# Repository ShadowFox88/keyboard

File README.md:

# Keyboard

This is a repo with the files used to make my own mechanical keyboard.

Why? It seemed like a fun project to do.

A journal of the time spent is available at report/report.pdf.

I used KiCad, and Fusion360 for this, and had to learn both of them.
All images are in the report.

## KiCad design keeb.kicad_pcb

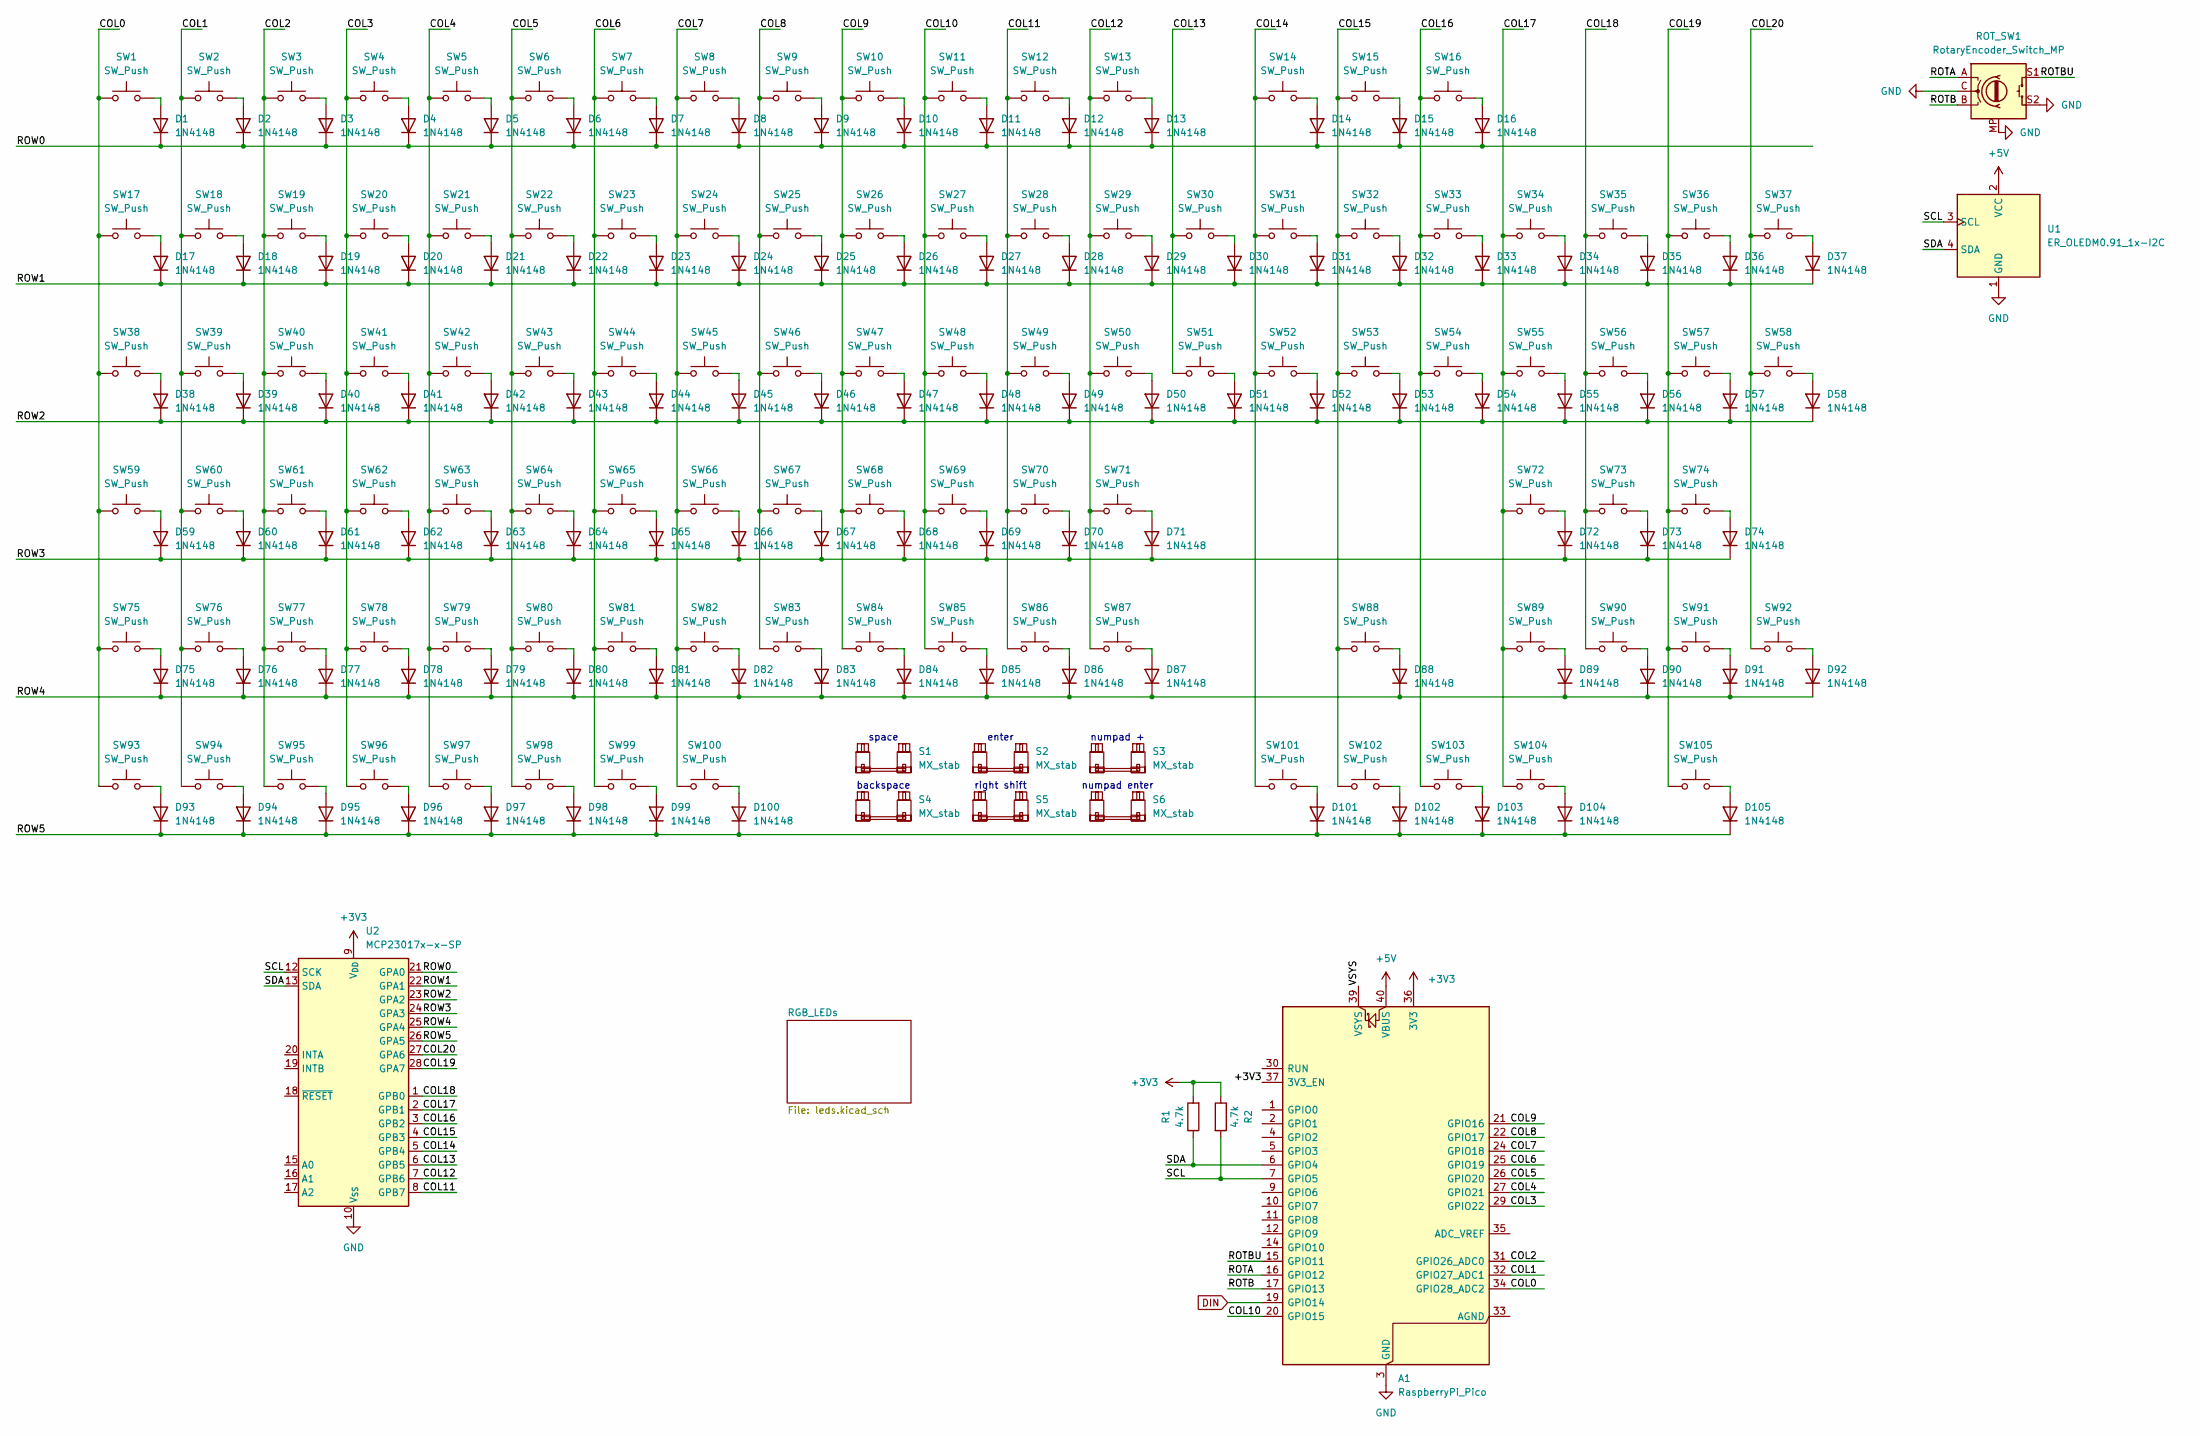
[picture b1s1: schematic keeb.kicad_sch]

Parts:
A1: RaspberryPi_Pico; RaspberryPi_Pico_Common_THT
D1, D2, D3, D4, D5, D6, D7, D8, D9, D10, D11, D12, D13, D14, D15, D16, D17, D18, D19, D20, D21, D22, D23, D24, D25, D26, D27, D28, D29, D30, D31, D32, D33, D34, D35, D36, D37, D38, D39, D40, D41, D42, D43, D44, D45, D46, D47, D48, D49, D50, D51, D52, D53, D54, D55, D56, D57, D58, D59, D60, D61, D62, D63, D64, D65, D66, D67, D68, D69, D70, D71, D72, D73, D74, D75, D76, D77, D78, D79, D80, D81, D82, D83, D84, D85, D86, D87, D88, D89, D90, D91, D92, D93, D94, D95, D96, D97, D98, D99, D100, D101, D102, D103, D104, D105: 1N4148; D_SOD-123F
R1, R2: 4.7k; R_Axial_DIN0207_L6.3mm_D2.5mm_P7.62mm_Horizontal
ROT_SW1: RotaryEncoder_Switch_MP; RotaryEncoder_Alps_EC12E-Switch_Vertical_H20mm
S1: MX_stab; STAB_MX_6.25u
S2: MX_stab; STAB_MX_ISO
S3, S4, S6: MX_stab; STAB_MX_2u
S5: MX_stab; STAB_MX_2.75u
SW1, SW2, SW3, SW4, SW5, SW6, SW7, SW8, SW9, SW10, SW11, SW12, SW13, SW14, SW15, SW16, SW17, SW18, SW19, SW20, SW21, SW22, SW23, SW24, SW25, SW26, SW27, SW28, SW29, SW30, SW31, SW32, SW33, SW34, SW35, SW36, SW37, SW38, SW39, SW40, SW41, SW42, SW43, SW44, SW45, SW46, SW47, SW48, SW49, SW50, SW51, SW52, SW53, SW54, SW55, SW56, SW57, SW58, SW59, SW60, SW61, SW62, SW63, SW64, SW65, SW66, SW67, SW68, SW69, SW70, SW71, SW72, SW73, SW74, SW75, SW76, SW77, SW78, SW79, SW80, SW81, SW82, SW83, SW84, SW85, SW86, SW87, SW88, SW89, SW90, SW91, SW92, SW93, SW94, SW95, SW96, SW97, SW98, SW99, SW100, SW101, SW102, SW103, SW104, SW105: SW_Push; SW_MX_HS_CPG151101S11_1u
U1: ER_OLEDM0.91_1x-I2C
U2: MCP23017x-x-SP; DIP-28_W7.62mm

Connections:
+3V3: A1.36 (3V3), A1.37 (3V3_EN), R1.2, R2.1, U2.9 (V_{DD})
+5V: A1.40 (VBUS), U1.2 (VCC); also elsewhere on the board
/COL0: A1.34 (GPIO28_ADC2), SW1.1, SW17.1, SW38.1, SW59.1, SW75.1, SW93.1
/COL1: A1.32 (GPIO27_ADC1), SW2.1, SW18.1, SW39.1, SW60.1, SW76.1, SW94.1
/COL2: A1.31 (GPIO26_ADC0), SW3.1, SW19.1, SW40.1, SW61.1, SW77.1, SW95.1
/COL3: A1.29 (GPIO22), SW4.1, SW20.1, SW41.1, SW62.1, SW78.1, SW96.1
/COL4: A1.27 (GPIO21), SW5.1, SW21.1, SW42.1, SW63.1, SW79.1, SW97.1
/COL5: A1.26 (GPIO20), SW6.1, SW22.1, SW43.1, SW64.1, SW80.1, SW98.1
/COL6: A1.25 (GPIO19), SW7.1, SW23.1, SW44.1, SW65.1, SW81.1, SW99.1
/COL7: A1.24 (GPIO18), SW8.1, SW24.1, SW45.1, SW66.1, SW82.1, SW100.1
/COL8: A1.22 (GPIO17), SW9.1, SW25.1, SW46.1, SW67.1, SW83.1
/COL9: A1.21 (GPIO16), SW10.1, SW26.1, SW47.1, SW68.1, SW84.1
/COL10: A1.20 (GPIO15), SW11.1, SW27.1, SW48.1, SW69.1, SW85.1
/COL11: SW12.1, SW28.1, SW49.1, SW70.1, SW86.1, U2.8 (GPB7)
/COL12: SW13.1, SW29.1, SW50.1, SW71.1, SW87.1, U2.7 (GPB6)
/COL13: SW30.1, SW51.1, U2.6 (GPB5)
/COL14: SW14.1, SW31.1, SW52.1, SW101.1, U2.5 (GPB4)
/COL15: SW15.1, SW32.1, SW53.1, SW88.1, SW102.1, U2.4 (GPB3)
/COL16: SW16.1, SW33.1, SW54.1, SW103.1, U2.3 (GPB2)
/COL17: SW34.1, SW55.1, SW72.1, SW89.1, SW104.1, U2.2 (GPB1)
/COL18: SW35.1, SW56.1, SW73.1, SW90.1, U2.1 (GPB0)
/COL19: SW36.1, SW57.1, SW74.1, SW91.1, SW105.1, U2.28 (GPA7)
/COL20: SW37.1, SW58.1, SW92.1, U2.27 (GPA6)
/ROTA: A1.16 (GPIO12), ROT_SW1.A
/ROTB: A1.17 (GPIO13), ROT_SW1.B
/ROTBU: A1.15 (GPIO11), ROT_SW1.S1
/ROW0: D1.1 (K), D2.1 (K), D3.1 (K), D4.1 (K), D5.1 (K), D6.1 (K), D7.1 (K), D8.1 (K), D9.1 (K), D10.1 (K), D11.1 (K), D12.1 (K), D13.1 (K), D14.1 (K), D15.1 (K), D16.1 (K), U2.21 (GPA0)
/ROW1: D17.1 (K), D18.1 (K), D19.1 (K), D20.1 (K), D21.1 (K), D22.1 (K), D23.1 (K), D24.1 (K), D25.1 (K), D26.1 (K), D27.1 (K), D28.1 (K), D29.1 (K), D30.1 (K), D31.1 (K), D32.1 (K), D33.1 (K), D34.1 (K), D35.1 (K), D36.1 (K), D37.1 (K), U2.22 (GPA1)
/ROW2: D38.1 (K), D39.1 (K), D40.1 (K), D41.1 (K), D42.1 (K), D43.1 (K), D44.1 (K), D45.1 (K), D46.1 (K), D47.1 (K), D48.1 (K), D49.1 (K), D50.1 (K), D51.1 (K), D52.1 (K), D53.1 (K), D54.1 (K), D55.1 (K), D56.1 (K), D57.1 (K), D58.1 (K), U2.23 (GPA2)
/ROW3: D59.1 (K), D60.1 (K), D61.1 (K), D62.1 (K), D63.1 (K), D64.1 (K), D65.1 (K), D66.1 (K), D67.1 (K), D68.1 (K), D69.1 (K), D70.1 (K), D71.1 (K), D72.1 (K), D73.1 (K), D74.1 (K), U2.24 (GPA3)
/ROW4: D75.1 (K), D76.1 (K), D77.1 (K), D78.1 (K), D79.1 (K), D80.1 (K), D81.1 (K), D82.1 (K), D83.1 (K), D84.1 (K), D85.1 (K), D86.1 (K), D87.1 (K), D88.1 (K), D89.1 (K), D90.1 (K), D91.1 (K), D92.1 (K), U2.25 (GPA4)
/ROW5: D93.1 (K), D94.1 (K), D95.1 (K), D96.1 (K), D97.1 (K), D98.1 (K), D99.1 (K), D100.1 (K), D101.1 (K), D102.1 (K), D103.1 (K), D104.1 (K), D105.1 (K), U2.26 (GPA5)
/SCL: A1.7 (GPIO5), R2.2, U1.3 (SCL), U2.12 (SCK)
/SDA: A1.6 (GPIO4), R1.1, U1.4 (SDA), U2.13 (SDA)
/VSYS: A1.39 (VSYS)
DIN: A1.19 (GPIO14); also elsewhere on the board
GND: A1.3 (GND), A1.8 (GND), A1.13 (GND), A1.18 (GND), A1.23 (GND), A1.28 (GND), A1.38 (GND), ROT_SW1.C, ROT_SW1.MP, ROT_SW1.S2, U1.1 (GND), U2.10 (V_{SS}); also elsewhere on the board
unnamed: D1.2 (A), SW1.2
unnamed: D2.2 (A), SW2.2
unnamed: D3.2 (A), SW3.2
unnamed: D4.2 (A), SW4.2
unnamed: D5.2 (A), SW5.2
unnamed: D6.2 (A), SW6.2
unnamed: D7.2 (A), SW7.2
unnamed: D8.2 (A), SW8.2
unnamed: D9.2 (A), SW9.2
unnamed: D10.2 (A), SW10.2
unnamed: D11.2 (A), SW11.2
unnamed: D12.2 (A), SW12.2
unnamed: D13.2 (A), SW13.2
unnamed: D14.2 (A), SW14.2
unnamed: D15.2 (A), SW15.2
unnamed: D16.2 (A), SW16.2
unnamed: D17.2 (A), SW17.2
unnamed: D18.2 (A), SW18.2
unnamed: D19.2 (A), SW19.2
unnamed: D20.2 (A), SW20.2
unnamed: D21.2 (A), SW21.2
unnamed: D22.2 (A), SW22.2
unnamed: D23.2 (A), SW23.2
unnamed: D24.2 (A), SW24.2
unnamed: D25.2 (A), SW25.2
unnamed: D26.2 (A), SW26.2
unnamed: D27.2 (A), SW27.2
unnamed: D28.2 (A), SW28.2
unnamed: D29.2 (A), SW29.2
unnamed: D30.2 (A), SW30.2
unnamed: D31.2 (A), SW31.2
unnamed: D32.2 (A), SW32.2
unnamed: D33.2 (A), SW33.2
unnamed: D34.2 (A), SW34.2
unnamed: D35.2 (A), SW35.2
unnamed: D36.2 (A), SW36.2
unnamed: D37.2 (A), SW37.2
unnamed: D38.2 (A), SW38.2
unnamed: D39.2 (A), SW39.2
unnamed: D40.2 (A), SW40.2
unnamed: D41.2 (A), SW41.2
unnamed: D42.2 (A), SW42.2
unnamed: D43.2 (A), SW43.2
unnamed: D44.2 (A), SW44.2
unnamed: D45.2 (A), SW45.2
unnamed: D46.2 (A), SW46.2
unnamed: D47.2 (A), SW47.2
unnamed: D48.2 (A), SW48.2
unnamed: D49.2 (A), SW49.2
unnamed: D50.2 (A), SW50.2
unnamed: D51.2 (A), SW51.2
unnamed: D52.2 (A), SW52.2
unnamed: D53.2 (A), SW53.2
unnamed: D54.2 (A), SW54.2
unnamed: D55.2 (A), SW55.2
unnamed: D56.2 (A), SW56.2
unnamed: D57.2 (A), SW57.2
unnamed: D58.2 (A), SW58.2
unnamed: D59.2 (A), SW59.2
unnamed: D60.2 (A), SW60.2
unnamed: D61.2 (A), SW61.2
unnamed: D62.2 (A), SW62.2
unnamed: D63.2 (A), SW63.2
unnamed: D64.2 (A), SW64.2
unnamed: D65.2 (A), SW65.2
unnamed: D66.2 (A), SW66.2
unnamed: D67.2 (A), SW67.2
unnamed: D68.2 (A), SW68.2
unnamed: D69.2 (A), SW69.2
unnamed: D70.2 (A), SW70.2
unnamed: D71.2 (A), SW71.2
unnamed: D72.2 (A), SW72.2
unnamed: D73.2 (A), SW73.2
unnamed: D74.2 (A), SW74.2
unnamed: D75.2 (A), SW75.2
unnamed: D76.2 (A), SW76.2
unnamed: D77.2 (A), SW77.2
unnamed: D78.2 (A), SW78.2
unnamed: D79.2 (A), SW79.2
unnamed: D80.2 (A), SW80.2
unnamed: D81.2 (A), SW81.2
unnamed: D82.2 (A), SW82.2
unnamed: D83.2 (A), SW83.2
unnamed: D84.2 (A), SW84.2
unnamed: D85.2 (A), SW85.2
unnamed: D86.2 (A), SW86.2
unnamed: D87.2 (A), SW87.2
unnamed: D88.2 (A), SW88.2
unnamed: D89.2 (A), SW89.2
unnamed: D90.2 (A), SW90.2
unnamed: D91.2 (A), SW91.2
unnamed: D92.2 (A), SW92.2
unnamed: D93.2 (A), SW93.2
unnamed: D94.2 (A), SW94.2
unnamed: D95.2 (A), SW95.2
unnamed: D96.2 (A), SW96.2
unnamed: D97.2 (A), SW97.2
unnamed: D98.2 (A), SW98.2
unnamed: D99.2 (A), SW99.2
unnamed: D100.2 (A), SW100.2
unnamed: D101.2 (A), SW101.2
unnamed: D102.2 (A), SW102.2
unnamed: D103.2 (A), SW103.2
unnamed: D104.2 (A), SW104.2
unnamed: D105.2 (A), SW105.2

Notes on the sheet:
numpad enter
numpad +
space
right shift
backspace
enter

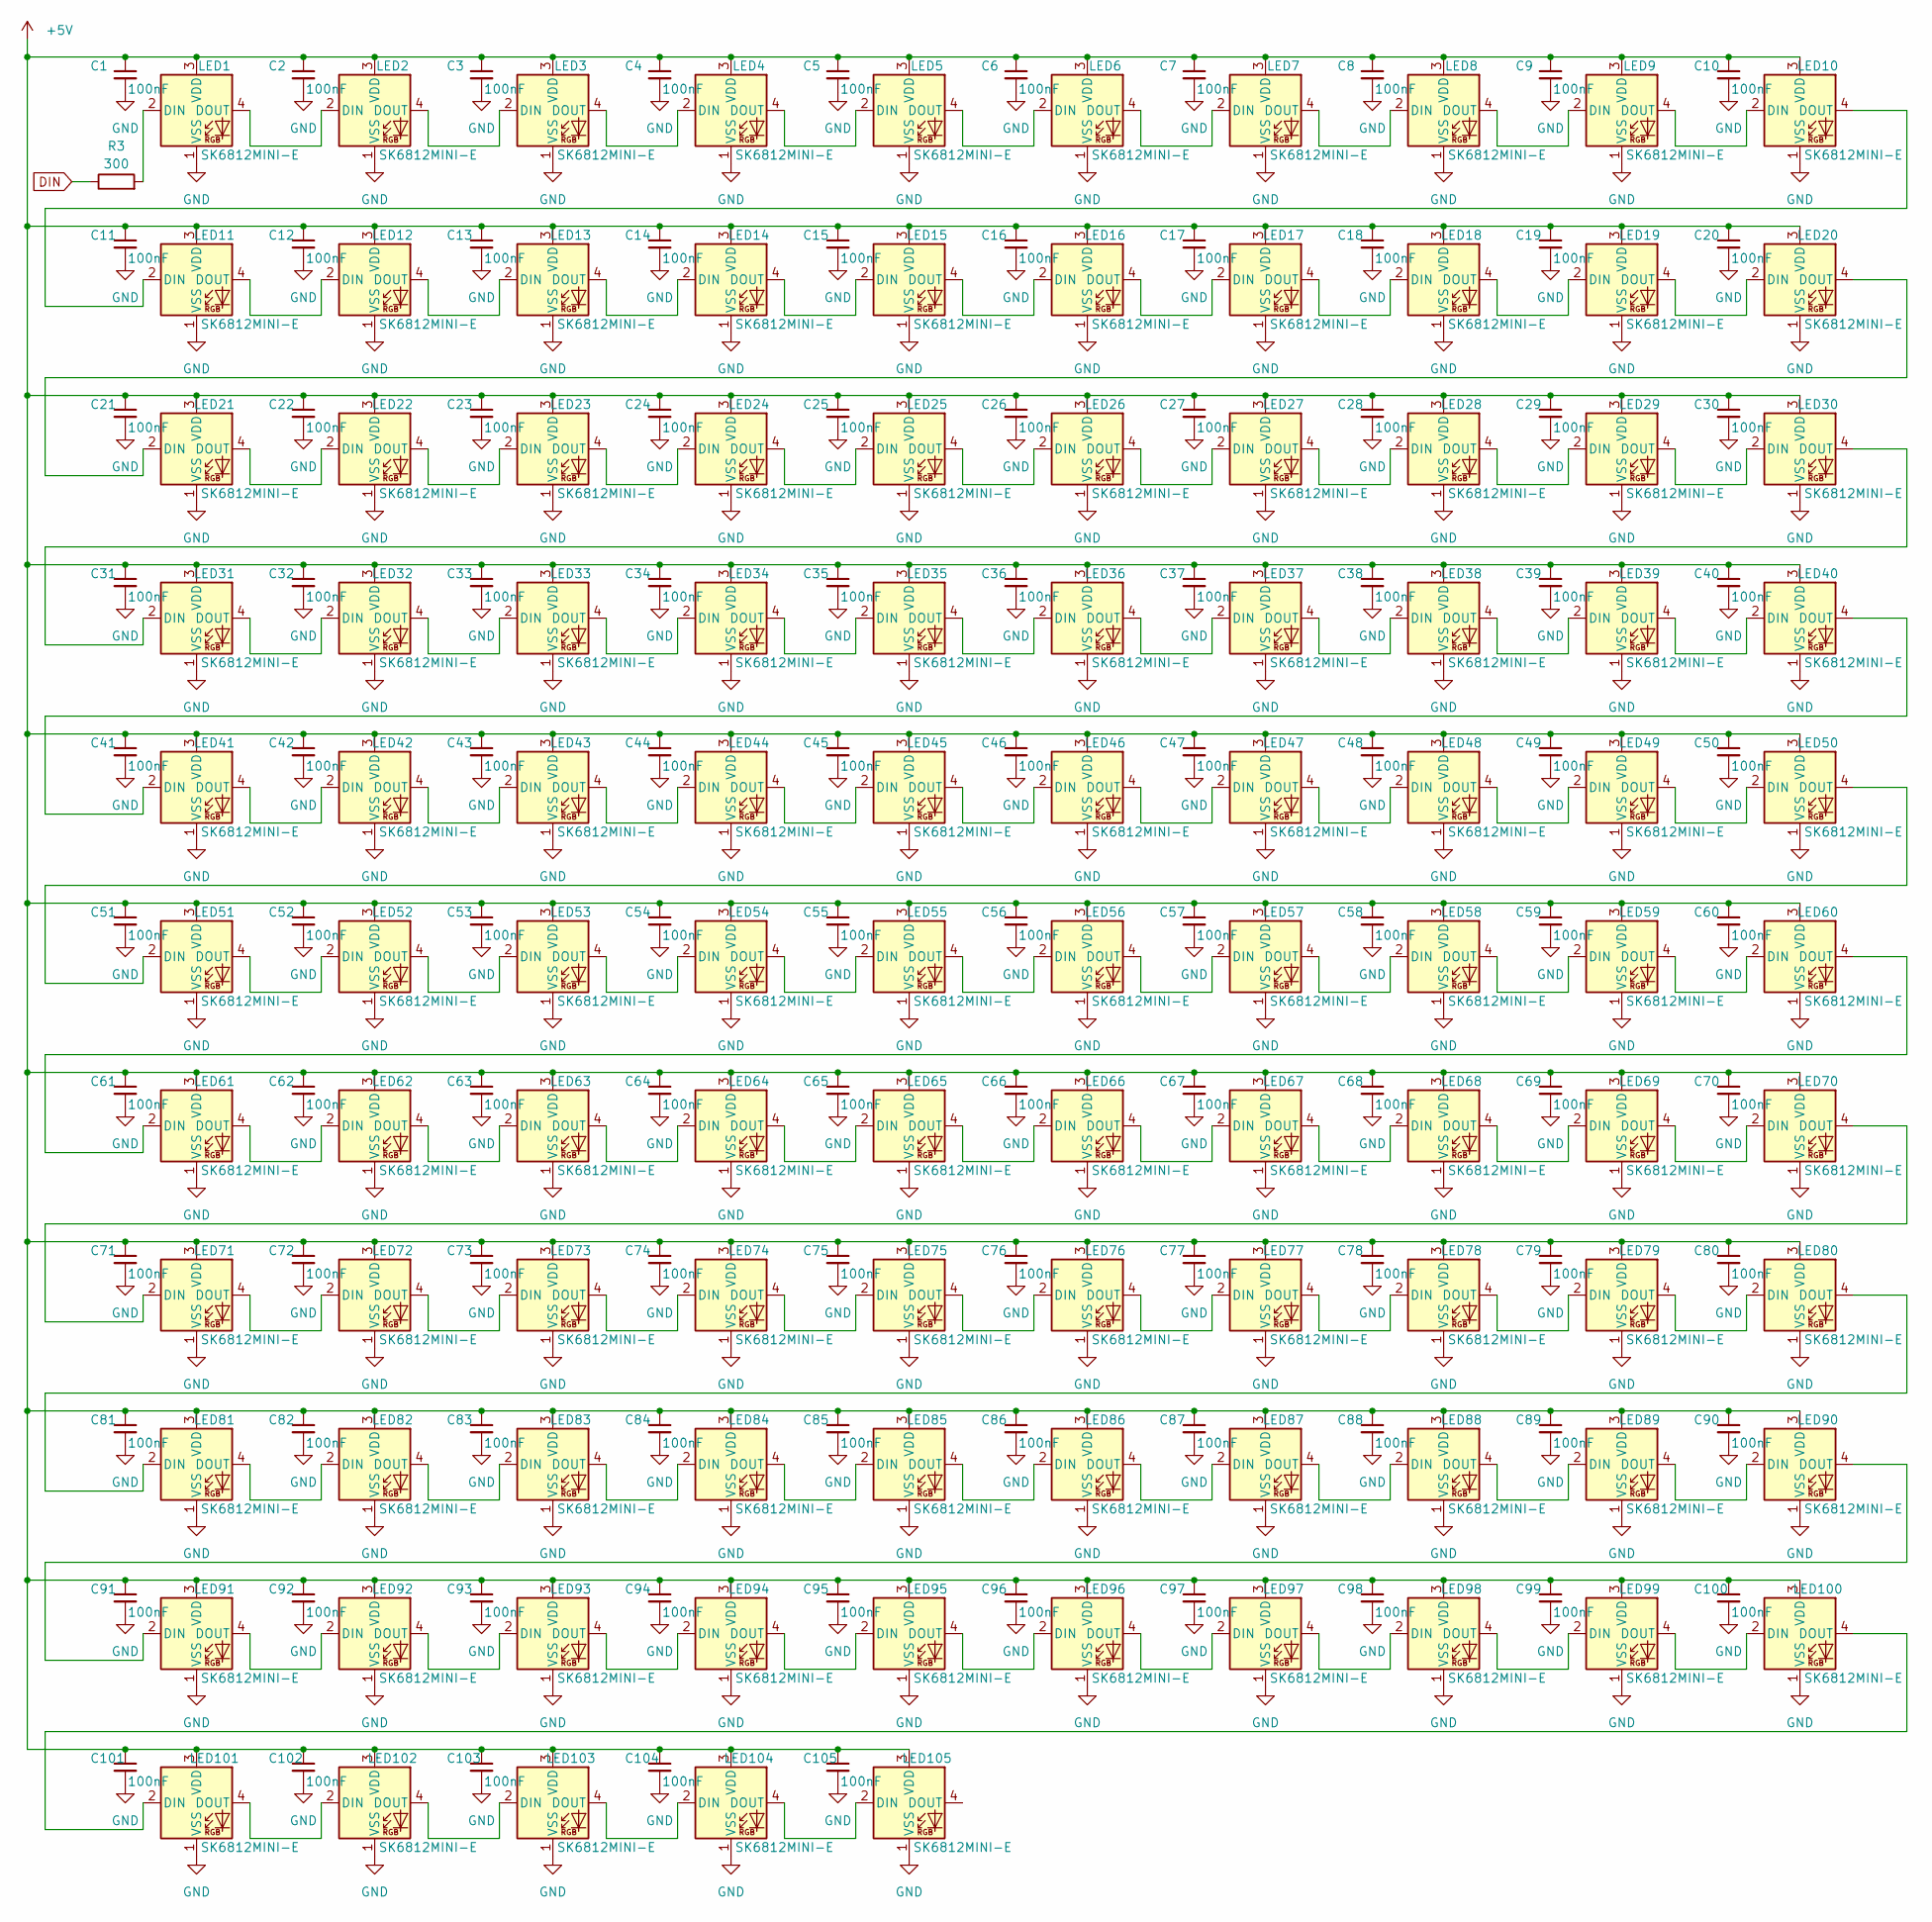
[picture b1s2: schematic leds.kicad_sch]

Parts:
C1, C2, C3, C4, C5, C6, C7, C8, C9, C10, C11, C12, C13, C14, C15, C16, C17, C18, C19, C20, C21, C22, C23, C24, C25, C26, C27, C28, C29, C30, C31, C32, C33, C34, C35, C36, C37, C38, C39, C40, C41, C42, C43, C44, C45, C46, C47, C48, C49, C50, C51, C52, C53, C54, C55, C56, C57, C58, C59, C60, C61, C62, C63, C64, C65, C66, C67, C68, C69, C70, C71, C72, C73, C74, C75, C76, C77, C78, C79, C80, C81, C82, C83, C84, C85, C86, C87, C88, C89, C90, C91, C92, C93, C94, C95, C96, C97, C98, C99, C100, C101, C102, C103, C104, C105: 100nF; C_1206_3216Metric_Pad1.33x1.80mm_HandSolder
LED1, LED2, LED3, LED4, LED5, LED6, LED7, LED8, LED9, LED10, LED11, LED12, LED13, LED14, LED15, LED16, LED17, LED18, LED19, LED20, LED21, LED22, LED23, LED24, LED25, LED26, LED27, LED28, LED29, LED30, LED31, LED32, LED33, LED34, LED35, LED36, LED37, LED38, LED39, LED40, LED41, LED42, LED43, LED44, LED45, LED46, LED47, LED48, LED49, LED50, LED51, LED52, LED53, LED54, LED55, LED56, LED57, LED58, LED59, LED60, LED61, LED62, LED63, LED64, LED65, LED66, LED67, LED68, LED69, LED70, LED71, LED72, LED73, LED74, LED75, LED76, LED77, LED78, LED79, LED80, LED81, LED82, LED83, LED84, LED85, LED86, LED87, LED88, LED89, LED90, LED91, LED92, LED93, LED94, LED95, LED96, LED97, LED98, LED99, LED100, LED101, LED102, LED103, LED104, LED105: SK6812MINI-E; LED_SK6812MINI-E_3.2x2.8mm_P1.5mm_ReverseMount
R3: 300; R_Axial_DIN0207_L6.3mm_D2.5mm_P7.62mm_Horizontal

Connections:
+5V: C1.1, C2.1, C3.1, C4.1, C5.1, C6.1, C7.1, C8.1, C9.1, C10.1, C11.1, C12.1, C13.1, C14.1, C15.1, C16.1, C17.1, C18.1, C19.1, C20.1, C21.1, C22.1, C23.1, C24.1, C25.1, C26.1, C27.1, C28.1, C29.1, C30.1, C31.1, C32.1, C33.1, C34.1, C35.1, C36.1, C37.1, C38.1, C39.1, C40.1, C41.1, C42.1, C43.1, C44.1, C45.1, C46.1, C47.1, C48.1, C49.1, C50.1, C51.1, C52.1, C53.1, C54.1, C55.1, C56.1, C57.1, C58.1, C59.1, C60.1, C61.1, C62.1, C63.1, C64.1, C65.1, C66.1, C67.1, C68.1, C69.1, C70.1, C71.1, C72.1, C73.1, C74.1, C75.1, C76.1, C77.1, C78.1, C79.1, C80.1, C81.1, C82.1, C83.1, C84.1, C85.1, C86.1, C87.1, C88.1, C89.1, C90.1, C91.1, C92.1, C93.1, C94.1, C95.1, C96.1, C97.1, C98.1, C99.1, C100.1, C101.1, C102.1, C103.1, C104.1, C105.1, LED1.3 (VDD), LED2.3 (VDD), LED3.3 (VDD), LED4.3 (VDD), LED5.3 (VDD), LED6.3 (VDD), LED7.3 (VDD), LED8.3 (VDD), LED9.3 (VDD), LED10.3 (VDD), LED11.3 (VDD), LED12.3 (VDD), LED13.3 (VDD), LED14.3 (VDD), LED15.3 (VDD), LED16.3 (VDD), LED17.3 (VDD), LED18.3 (VDD), LED19.3 (VDD), LED20.3 (VDD), LED21.3 (VDD), LED22.3 (VDD), LED23.3 (VDD), LED24.3 (VDD), LED25.3 (VDD), LED26.3 (VDD), LED27.3 (VDD), LED28.3 (VDD), LED29.3 (VDD), LED30.3 (VDD), LED31.3 (VDD), LED32.3 (VDD), LED33.3 (VDD), LED34.3 (VDD), LED35.3 (VDD), LED36.3 (VDD), LED37.3 (VDD), LED38.3 (VDD), LED39.3 (VDD), LED40.3 (VDD), LED41.3 (VDD), LED42.3 (VDD), LED43.3 (VDD), LED44.3 (VDD), LED45.3 (VDD), LED46.3 (VDD), LED47.3 (VDD), LED48.3 (VDD), LED49.3 (VDD), LED50.3 (VDD), LED51.3 (VDD), LED52.3 (VDD), LED53.3 (VDD), LED54.3 (VDD), LED55.3 (VDD), LED56.3 (VDD), LED57.3 (VDD), LED58.3 (VDD), LED59.3 (VDD), LED60.3 (VDD), LED61.3 (VDD), LED62.3 (VDD), LED63.3 (VDD), LED64.3 (VDD), LED65.3 (VDD), LED66.3 (VDD), LED67.3 (VDD), LED68.3 (VDD), LED69.3 (VDD), LED70.3 (VDD), LED71.3 (VDD), LED72.3 (VDD), LED73.3 (VDD), LED74.3 (VDD), LED75.3 (VDD), LED76.3 (VDD), LED77.3 (VDD), LED78.3 (VDD), LED79.3 (VDD), LED80.3 (VDD), LED81.3 (VDD), LED82.3 (VDD), LED83.3 (VDD), LED84.3 (VDD), LED85.3 (VDD), LED86.3 (VDD), LED87.3 (VDD), LED88.3 (VDD), LED89.3 (VDD), LED90.3 (VDD), LED91.3 (VDD), LED92.3 (VDD), LED93.3 (VDD), LED94.3 (VDD), LED95.3 (VDD), LED96.3 (VDD), LED97.3 (VDD), LED98.3 (VDD), LED99.3 (VDD), LED100.3 (VDD), LED101.3 (VDD), LED102.3 (VDD), LED103.3 (VDD), LED104.3 (VDD), LED105.3 (VDD); also elsewhere on the board
DIN: R3.1; also elsewhere on the board
GND: C1.2, C2.2, C3.2, C4.2, C5.2, C6.2, C7.2, C8.2, C9.2, C10.2, C11.2, C12.2, C13.2, C14.2, C15.2, C16.2, C17.2, C18.2, C19.2, C20.2, C21.2, C22.2, C23.2, C24.2, C25.2, C26.2, C27.2, C28.2, C29.2, C30.2, C31.2, C32.2, C33.2, C34.2, C35.2, C36.2, C37.2, C38.2, C39.2, C40.2, C41.2, C42.2, C43.2, C44.2, C45.2, C46.2, C47.2, C48.2, C49.2, C50.2, C51.2, C52.2, C53.2, C54.2, C55.2, C56.2, C57.2, C58.2, C59.2, C60.2, C61.2, C62.2, C63.2, C64.2, C65.2, C66.2, C67.2, C68.2, C69.2, C70.2, C71.2, C72.2, C73.2, C74.2, C75.2, C76.2, C77.2, C78.2, C79.2, C80.2, C81.2, C82.2, C83.2, C84.2, C85.2, C86.2, C87.2, C88.2, C89.2, C90.2, C91.2, C92.2, C93.2, C94.2, C95.2, C96.2, C97.2, C98.2, C99.2, C100.2, C101.2, C102.2, C103.2, C104.2, C105.2, LED1.1 (VSS), LED2.1 (VSS), LED3.1 (VSS), LED4.1 (VSS), LED5.1 (VSS), LED6.1 (VSS), LED7.1 (VSS), LED8.1 (VSS), LED9.1 (VSS), LED10.1 (VSS), LED11.1 (VSS), LED12.1 (VSS), LED13.1 (VSS), LED14.1 (VSS), LED15.1 (VSS), LED16.1 (VSS), LED17.1 (VSS), LED18.1 (VSS), LED19.1 (VSS), LED20.1 (VSS), LED21.1 (VSS), LED22.1 (VSS), LED23.1 (VSS), LED24.1 (VSS), LED25.1 (VSS), LED26.1 (VSS), LED27.1 (VSS), LED28.1 (VSS), LED29.1 (VSS), LED30.1 (VSS), LED31.1 (VSS), LED32.1 (VSS), LED33.1 (VSS), LED34.1 (VSS), LED35.1 (VSS), LED36.1 (VSS), LED37.1 (VSS), LED38.1 (VSS), LED39.1 (VSS), LED40.1 (VSS), LED41.1 (VSS), LED42.1 (VSS), LED43.1 (VSS), LED44.1 (VSS), LED45.1 (VSS), LED46.1 (VSS), LED47.1 (VSS), LED48.1 (VSS), LED49.1 (VSS), LED50.1 (VSS), LED51.1 (VSS), LED52.1 (VSS), LED53.1 (VSS), LED54.1 (VSS), LED55.1 (VSS), LED56.1 (VSS), LED57.1 (VSS), LED58.1 (VSS), LED59.1 (VSS), LED60.1 (VSS), LED61.1 (VSS), LED62.1 (VSS), LED63.1 (VSS), LED64.1 (VSS), LED65.1 (VSS), LED66.1 (VSS), LED67.1 (VSS), LED68.1 (VSS), LED69.1 (VSS), LED70.1 (VSS), LED71.1 (VSS), LED72.1 (VSS), LED73.1 (VSS), LED74.1 (VSS), LED75.1 (VSS), LED76.1 (VSS), LED77.1 (VSS), LED78.1 (VSS), LED79.1 (VSS), LED80.1 (VSS), LED81.1 (VSS), LED82.1 (VSS), LED83.1 (VSS), LED84.1 (VSS), LED85.1 (VSS), LED86.1 (VSS), LED87.1 (VSS), LED88.1 (VSS), LED89.1 (VSS), LED90.1 (VSS), LED91.1 (VSS), LED92.1 (VSS), LED93.1 (VSS), LED94.1 (VSS), LED95.1 (VSS), LED96.1 (VSS), LED97.1 (VSS), LED98.1 (VSS), LED99.1 (VSS), LED100.1 (VSS), LED101.1 (VSS), LED102.1 (VSS), LED103.1 (VSS), LED104.1 (VSS), LED105.1 (VSS); also elsewhere on the board
unnamed: LED1.2 (DIN), R3.2
unnamed: LED1.4 (DOUT), LED2.2 (DIN)
unnamed: LED2.4 (DOUT), LED3.2 (DIN)
unnamed: LED3.4 (DOUT), LED4.2 (DIN)
unnamed: LED4.4 (DOUT), LED5.2 (DIN)
unnamed: LED5.4 (DOUT), LED6.2 (DIN)
unnamed: LED6.4 (DOUT), LED7.2 (DIN)
unnamed: LED7.4 (DOUT), LED8.2 (DIN)
unnamed: LED8.4 (DOUT), LED9.2 (DIN)
unnamed: LED9.4 (DOUT), LED10.2 (DIN)
unnamed: LED10.4 (DOUT), LED11.2 (DIN)
unnamed: LED11.4 (DOUT), LED12.2 (DIN)
unnamed: LED12.4 (DOUT), LED13.2 (DIN)
unnamed: LED13.4 (DOUT), LED14.2 (DIN)
unnamed: LED14.4 (DOUT), LED15.2 (DIN)
unnamed: LED15.4 (DOUT), LED16.2 (DIN)
unnamed: LED16.4 (DOUT), LED17.2 (DIN)
unnamed: LED17.4 (DOUT), LED18.2 (DIN)
unnamed: LED18.4 (DOUT), LED19.2 (DIN)
unnamed: LED19.4 (DOUT), LED20.2 (DIN)
unnamed: LED20.4 (DOUT), LED21.2 (DIN)
unnamed: LED21.4 (DOUT), LED22.2 (DIN)
unnamed: LED22.4 (DOUT), LED23.2 (DIN)
unnamed: LED23.4 (DOUT), LED24.2 (DIN)
unnamed: LED24.4 (DOUT), LED25.2 (DIN)
unnamed: LED25.4 (DOUT), LED26.2 (DIN)
unnamed: LED26.4 (DOUT), LED27.2 (DIN)
unnamed: LED27.4 (DOUT), LED28.2 (DIN)
unnamed: LED28.4 (DOUT), LED29.2 (DIN)
unnamed: LED29.4 (DOUT), LED30.2 (DIN)
unnamed: LED30.4 (DOUT), LED31.2 (DIN)
unnamed: LED31.4 (DOUT), LED32.2 (DIN)
unnamed: LED32.4 (DOUT), LED33.2 (DIN)
unnamed: LED33.4 (DOUT), LED34.2 (DIN)
unnamed: LED34.4 (DOUT), LED35.2 (DIN)
unnamed: LED35.4 (DOUT), LED36.2 (DIN)
unnamed: LED36.4 (DOUT), LED37.2 (DIN)
unnamed: LED37.4 (DOUT), LED38.2 (DIN)
unnamed: LED38.4 (DOUT), LED39.2 (DIN)
unnamed: LED39.4 (DOUT), LED40.2 (DIN)
unnamed: LED40.4 (DOUT), LED41.2 (DIN)
unnamed: LED41.4 (DOUT), LED42.2 (DIN)
unnamed: LED42.4 (DOUT), LED43.2 (DIN)
unnamed: LED43.4 (DOUT), LED44.2 (DIN)
unnamed: LED44.4 (DOUT), LED45.2 (DIN)
unnamed: LED45.4 (DOUT), LED46.2 (DIN)
unnamed: LED46.4 (DOUT), LED47.2 (DIN)
unnamed: LED47.4 (DOUT), LED48.2 (DIN)
unnamed: LED48.4 (DOUT), LED49.2 (DIN)
unnamed: LED49.4 (DOUT), LED50.2 (DIN)
unnamed: LED50.4 (DOUT), LED51.2 (DIN)
unnamed: LED51.4 (DOUT), LED52.2 (DIN)
unnamed: LED52.4 (DOUT), LED53.2 (DIN)
unnamed: LED53.4 (DOUT), LED54.2 (DIN)
unnamed: LED54.4 (DOUT), LED55.2 (DIN)
unnamed: LED55.4 (DOUT), LED56.2 (DIN)
unnamed: LED56.4 (DOUT), LED57.2 (DIN)
unnamed: LED57.4 (DOUT), LED58.2 (DIN)
unnamed: LED58.4 (DOUT), LED59.2 (DIN)
unnamed: LED59.4 (DOUT), LED60.2 (DIN)
unnamed: LED60.4 (DOUT), LED61.2 (DIN)
unnamed: LED61.4 (DOUT), LED62.2 (DIN)
unnamed: LED62.4 (DOUT), LED63.2 (DIN)
unnamed: LED63.4 (DOUT), LED64.2 (DIN)
unnamed: LED64.4 (DOUT), LED65.2 (DIN)
unnamed: LED65.4 (DOUT), LED66.2 (DIN)
unnamed: LED66.4 (DOUT), LED67.2 (DIN)
unnamed: LED67.4 (DOUT), LED68.2 (DIN)
unnamed: LED68.4 (DOUT), LED69.2 (DIN)
unnamed: LED69.4 (DOUT), LED70.2 (DIN)
unnamed: LED70.4 (DOUT), LED71.2 (DIN)
unnamed: LED71.4 (DOUT), LED72.2 (DIN)
unnamed: LED72.4 (DOUT), LED73.2 (DIN)
unnamed: LED73.4 (DOUT), LED74.2 (DIN)
unnamed: LED74.4 (DOUT), LED75.2 (DIN)
unnamed: LED75.4 (DOUT), LED76.2 (DIN)
unnamed: LED76.4 (DOUT), LED77.2 (DIN)
unnamed: LED77.4 (DOUT), LED78.2 (DIN)
unnamed: LED78.4 (DOUT), LED79.2 (DIN)
unnamed: LED79.4 (DOUT), LED80.2 (DIN)
unnamed: LED80.4 (DOUT), LED81.2 (DIN)
unnamed: LED81.4 (DOUT), LED82.2 (DIN)
unnamed: LED82.4 (DOUT), LED83.2 (DIN)
unnamed: LED83.4 (DOUT), LED84.2 (DIN)
unnamed: LED84.4 (DOUT), LED85.2 (DIN)
unnamed: LED85.4 (DOUT), LED86.2 (DIN)
unnamed: LED86.4 (DOUT), LED87.2 (DIN)
unnamed: LED87.4 (DOUT), LED88.2 (DIN)
unnamed: LED88.4 (DOUT), LED89.2 (DIN)
unnamed: LED89.4 (DOUT), LED90.2 (DIN)
unnamed: LED90.4 (DOUT), LED91.2 (DIN)
unnamed: LED91.4 (DOUT), LED92.2 (DIN)
unnamed: LED92.4 (DOUT), LED93.2 (DIN)
unnamed: LED93.4 (DOUT), LED94.2 (DIN)
unnamed: LED94.4 (DOUT), LED95.2 (DIN)
unnamed: LED95.4 (DOUT), LED96.2 (DIN)
unnamed: LED96.4 (DOUT), LED97.2 (DIN)
unnamed: LED97.4 (DOUT), LED98.2 (DIN)
unnamed: LED98.4 (DOUT), LED99.2 (DIN)
unnamed: LED99.4 (DOUT), LED100.2 (DIN)
unnamed: LED100.4 (DOUT), LED101.2 (DIN)
unnamed: LED101.4 (DOUT), LED102.2 (DIN)
unnamed: LED102.4 (DOUT), LED103.2 (DIN)
unnamed: LED103.4 (DOUT), LED104.2 (DIN)
unnamed: LED104.4 (DOUT), LED105.2 (DIN)

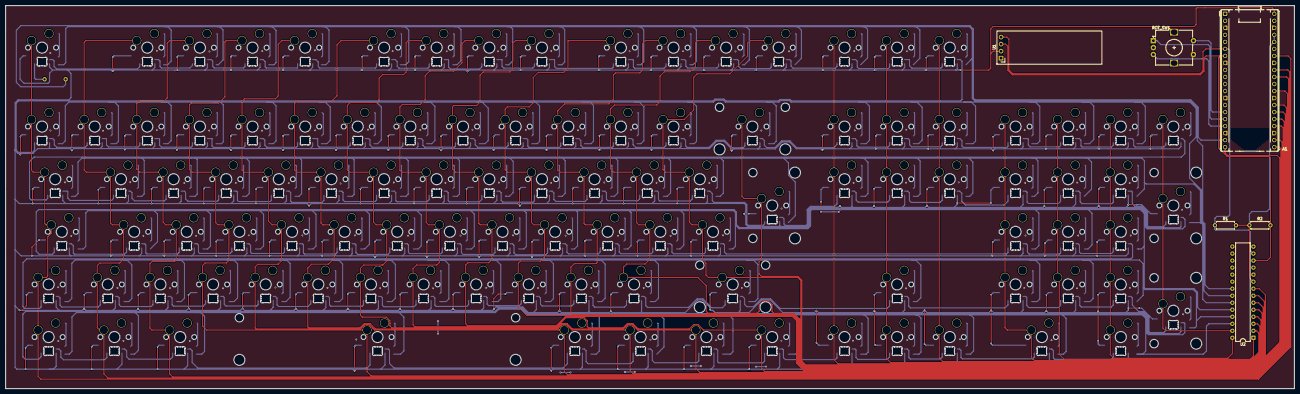
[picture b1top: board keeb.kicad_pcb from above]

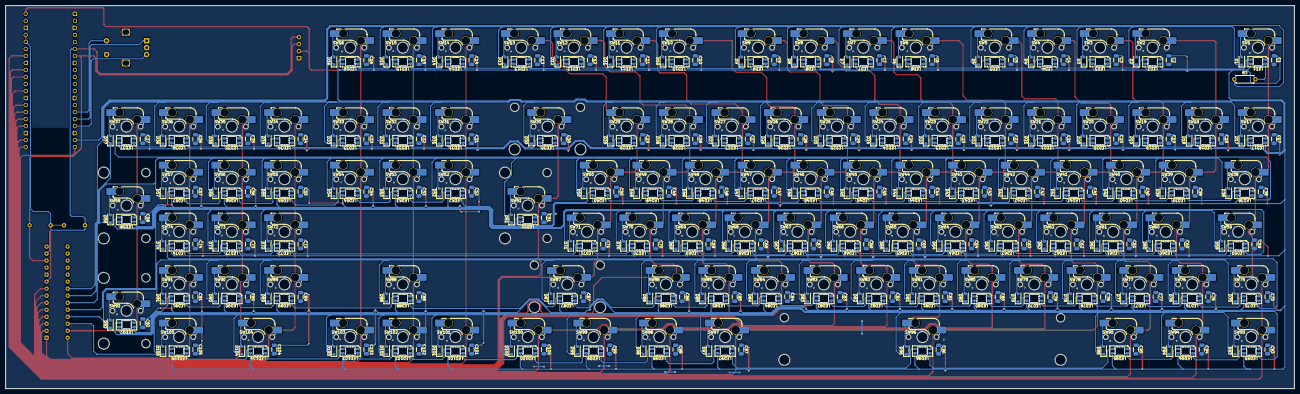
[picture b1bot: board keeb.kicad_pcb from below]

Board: 2 copper layers, 466.6 x 138.7 mm, 433 parts (421 on the bottom side), 246 nets.

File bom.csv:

Reference,Qty,Value,DNP,Exclude from BOM,Exclude from Board,Notes/Buying Location
A1,1,RaspberryPi_Pico,,,,orpheus pico - check hc
"C1,C2,C3,C4,C5,C6,C7,C8,C9,C10,C11,C12,C13,C14,C15,C16,C17,C18,C19,C20,C21,C22,C23,C24,C25,C26,C27,C28,C29,C30,C31,C32,C33,C34,C35,C36,C37,C38,C39,C40,C41,C42,C43,C44,C45,C46,C47,C48,C49,C50,C51,C52,C53,C54,C55,C56,C57,C58,C59,C60,C61,C62,C63,C64,C65,C66,C67,C68,C69,C70,C71,C72,C73,C74,C75,C76,C77,C78,C79,C80,C81,C82,C83,C84,C85,C86,C87,C88,C89,C90,C91,C92,C93,C94,C95,C96,C97,C98,C99,C100,C101,C102,C103,C104,C105",105,100nF,,,,https://www.aliexpress.com/item/1005007470747384.html
"D1,D2,D3,D4,D5,D6,D7,D8,D9,D10,D11,D12,D13,D14,D15,D16,D17,D18,D19,D20,D21,D22,D23,D24,D25,D26,D27,D28,D29,D30,D31,D32,D33,D34,D35,D36,D37,D38,D39,D40,D41,D42,D43,D44,D45,D46,D47,D48,D49,D50,D51,D52,D53,D54,D55,D56,D57,D58,D59,D60,D61,D62,D63,D64,D65,D66,D67,D68,D69,D70,D71,D72,D73,D74,D75,D76,D77,D78,D79,D80,D81,D82,D83,D84,D85,D86,D87,D88,D89,D90,D91,D92,D93,D94,D95,D96,D97,D98,D99,D100,D101,D102,D103,D104,D105",105,1N4148,,,,https://www.aliexpress.com/item/1005006323468521.html
"LED1,LED2,LED3,LED4,LED5,LED6,LED7,LED8,LED9,LED10,LED11,LED12,LED13,LED14,LED15,LED16,LED17,LED18,LED19,LED20,LED21,LED22,LED23,LED24,LED25,LED26,LED27,LED28,LED29,LED30,LED31,LED32,LED33,LED34,LED35,LED36,LED37,LED38,LED39,LED40,LED41,LED42,LED43,LED44,LED45,LED46,LED47,LED48,LED49,LED50,LED51,LED52,LED53,LED54,LED55,LED56,LED57,LED58,LED59,LED60,LED61,LED62,LED63,LED64,LED65,LED66,LED67,LED68,LED69,LED70,LED71,LED72,LED73,LED74,LED75,LED76,LED77,LED78,LED79,LED80,LED81,LED82,LED83,LED84,LED85,LED86,LED87,LED88,LED89,LED90,LED91,LED92,LED93,LED94,LED95,LED96,LED97,LED98,LED99,LED100,LED101,LED102,LED103,LED104,LED105",105,SK6812MINI-E,,,,https://www.lcsc.com/product-detail/C5149201.html?s_z=n_SK68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
"R1,R2",2,4.7k,,,,own these
R3,1,300,,,,own these
ROT_SW1,1,RotaryEncoder_Switch_MP,,,,https://www.aliexpress.com/item/1005006136446310.html
"SW1,SW2,SW3,SW4,SW5,SW6,SW7,SW8,SW9,SW10,SW11,SW12,SW13,SW14,SW15,SW16,SW17,SW18,SW19,SW20,SW21,SW22,SW23,SW24,SW25,SW26,SW27,SW28,SW29,SW30,SW31,SW32,SW33,SW34,SW35,SW36,SW37,SW38,SW39,SW40,SW41,SW42,SW43,SW44,SW45,SW46,SW47,SW48,SW49,SW50,SW51,SW52,SW53,SW54,SW55,SW56,SW57,SW58,SW59,SW60,SW61,SW62,SW63,SW64,SW65,SW66,SW67,SW68,SW69,SW70,SW71,SW72,SW73,SW74,SW75,SW76,SW77,SW78,SW79,SW80,SW81,SW82,SW83,SW84,SW85,SW86,SW87,SW88,SW89,SW90,SW91,SW92,SW93,SW94,SW95,SW96,SW97,SW98,SW99,SW100,SW101,SW102,SW103,SW104,SW105",105,SW_Push,,,,https://www.aliexpress.com/item/1005002378701948.html
U1,1,ER_OLEDM0.91_1x-I2C,,,,https://www.aliexpress.com/item/32836691660.html
U2,1,MCP23017x-x-SP,,,,https://www.aliexpress.com/item/1005009506514213.html
